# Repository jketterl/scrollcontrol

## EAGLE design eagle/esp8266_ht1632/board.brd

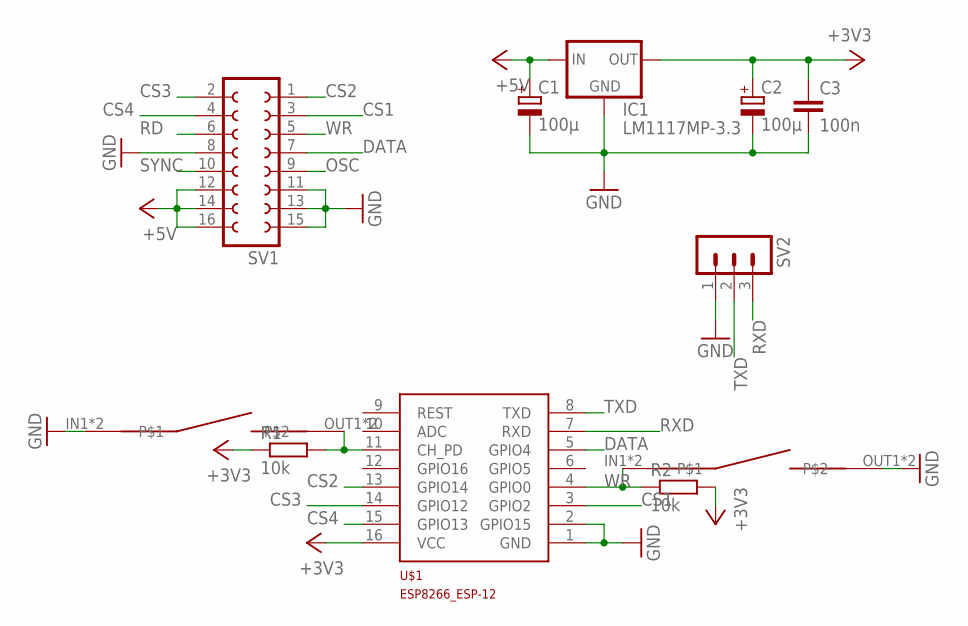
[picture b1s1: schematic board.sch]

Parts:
C1, C2: 100µ; E2,5-6
C3: 100n; C0805
IC1: LM1117MP-3.3; SOT223
R1, R2: 10k; R0805
SV1: FE08-2
SV2: MA03-1
U$1: ESP8266_ESP-12; ESP8266-ESP12
U$2, U$3: KMR221

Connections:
+3V3: C2.+, C3.1, IC1.2 (OUT), IC1.4 (OUT), R1.1, R2.2, U$1.16 (VCC)
+5V: C1.+, IC1.3 (IN), SV1.12, SV1.14, SV1.16
CS1: SV1.3, U$1.3 (GPIO2)
CS2: SV1.1, U$1.13 (GPIO14)
CS3: SV1.2, U$1.14 (GPIO12)
CS4: SV1.4, U$1.15 (GPIO13)
DATA: SV1.7, U$1.5 (GPIO4)
GND: C1.-, C2.-, C3.2, IC1.1 (GND), SV1.8, SV1.11, SV1.13, SV1.15, SV2.1, U$1.1 (GND), U$1.2 (GPIO15), U$2.IN1, U$2.IN2, U$3.OUT1, U$3.OUT2
unnamed: R1.2, U$1.11 (CH_PD), U$2.OUT1, U$2.OUT2
OSC: SV1.9
RD: SV1.6
RXD: SV2.3, U$1.7 (RXD)
SYNC: SV1.10
TXD: SV2.2, U$1.8 (TXD)
WR: R2.1, SV1.5, U$1.4 (GPIO0), U$3.IN1, U$3.IN2

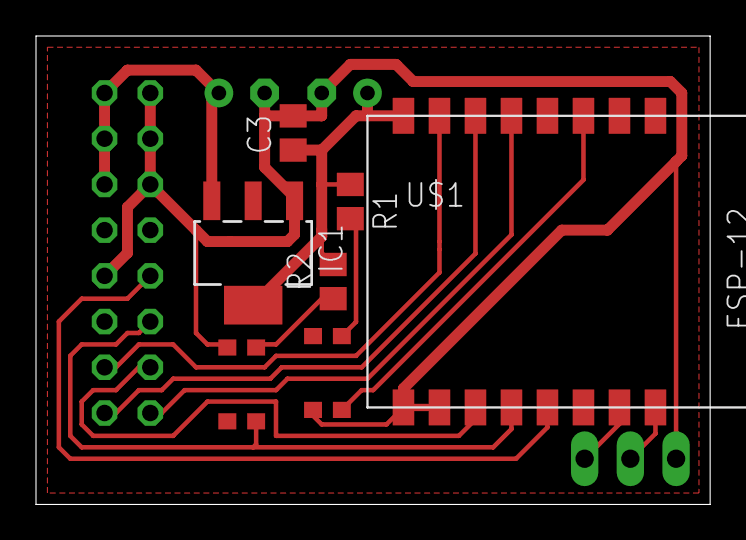
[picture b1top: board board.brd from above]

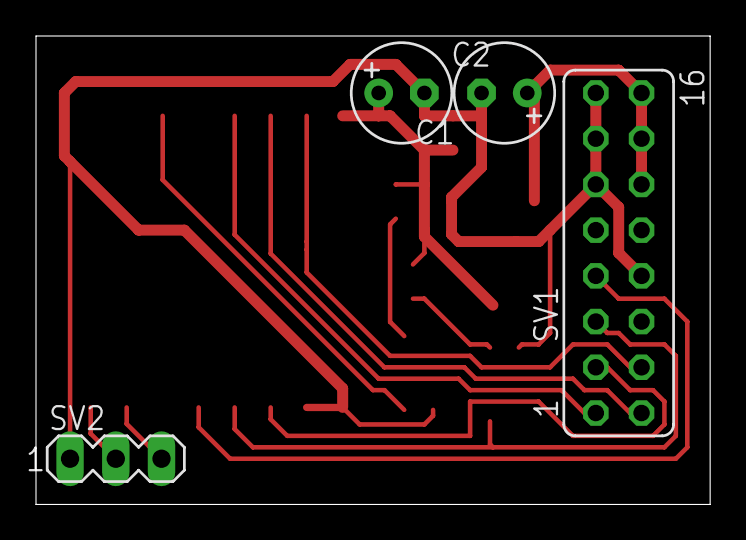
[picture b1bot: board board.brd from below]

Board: 2 copper layers, 37.5 x 26.0 mm, 11 parts (4 on the bottom side), 12 nets.

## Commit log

2013-11-10 initial import
2013-11-10 restore the arduino code
2013-11-10 make class files possible
2013-11-10 add a navigation menu
2013-11-12 make use of the activity led on board
2013-11-12 implement the multi-step editor in the gui
2013-11-12 implement step removal & auto-select new steps on addition
2013-11-14 first steps integrating mongodb
2013-11-16 add associated data to the ext writer, so be able to save the whole record at once
2013-11-17 finish implement creating & updating & direct send from list
2013-11-17 remove the name from the grid and display a textual sum-up instead
2013-11-17 move the code out into a separate file
2013-11-17 add buttons to the top of the grid, implement sequence deletion
2013-11-17 add icons & a "new sequence" button
2013-11-17 make space for animation steps
2013-11-17 optimize
2013-11-19 run on 4 displays
2013-11-19 show the list of sequences by default
2013-11-19 pass sequene objects & move the logic to build the binary form
2013-11-19 move to ino build system
2013-11-19 add firmware upload script
2013-11-19 auto-compile
2013-11-19 fix direct mode
2013-11-19 add animation data to binary format
2013-11-20 first steps with animation objects
2013-11-20 add database repair script
2013-11-20 shutdown db before repair
2013-11-22 implement all the different animations
2013-11-22 fix memory management
2013-11-22 make all animations center-aligned
2013-11-22 new default animation
2013-11-22 remove console output
2013-11-22 increase chunk size
2013-11-22 re-add led signaling for data reception wait for input
2013-11-22 fix timing
2013-11-22 handle drain events
2013-11-22 remove the speed
2013-11-22 use delete() instead of free() for objects
2013-11-22 automatic database repair on startup
2013-11-22 implement animation removal
2015-03-06 implement remote displays (for arduino yun) via tcp sockets
2015-03-06 remove closed connections
2015-03-06 start sequence with double click
2015-03-07 fix initial database repair
2015-03-21 arduino yun connection reversal
2015-03-21 improve error handling
2017-04-14 sort existing sketches
2017-04-14 remove obsolete structure
2017-04-14 add first steps for esp8266 code
2017-04-14 move the server code to a separate folder, too
2017-04-14 add npm dependencies
2017-04-14 start integrating wifi
2017-04-14 new style bodyparser
2017-04-14 add ext symlink
2017-04-14 remove locally connected display
2017-04-14 add famfamfam icon set as npm dependency
2017-04-14 add extjs to ignored files
2017-04-15 implement automatic server detection - server side
2017-04-15 implement automatic server detection - client side
2017-04-15 add proper calculation of broadcast address
2017-04-15 add eagle files for the first controller board
2017-04-15 resize board; add gitignore for eagle
2017-04-15 move files to lib folder
2017-04-16 board optimization; fix esp pinout
2017-04-16 ratsnest
2017-04-16 GPIO15 to GND to allow bootloading /bin/bash: q: command not found
2017-04-17 text length is now 16bit
2017-04-17 parse new 3-byte header allowing messages of up to 65535 characters
2017-04-19 disable word wrap
2017-06-04 add some essential configuration for running a access point on a raspberry
2017-06-04 add supervisor conf, too
